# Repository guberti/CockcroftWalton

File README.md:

# 40 kV 10 mA Cockcroft-Walton Multiplier
To power a Farnsworth-Hirsch fusor me and some other [@EastsidePreparatorySchool](https://github.com/EastsidePreparatorySchool) students are building, we calculated we would need 10 mA of DC current, since the amount of radiation produced is proportional to the **square** of the voltage.

In this repo you can see the files needed to edit and order these circuit boards yourself. They are in EAGLE CAD format, and a ZIP file accepted by circuit board makers is also provided. 

The Cockcroft-Walton multiplier here is a two-stage full-wave multiplier. It is intended to be powered by a neon sign transformer that supplies 24 kV peak-to-peak AC at 30 mA in alternating phases. These are pretty cheap, and can be had on Ebay for ~$150. Note that you will need to remove the safety features of the NST before it can power these multipliers.

The circuit board, as printed, transforms this into +35 kV DC at 10 mA, though I intentionally installed the diodes backwards in my multiplier so it produces -35 kV instead (this is needed for deuterium fusion, since these ions are positively charged).

<p align="center"><i>Two stages of the soldered board. Blue jumper wires are present to stop the capacitors from building up charge.</i></p>

<p align="center"><i>The circuit board in EAGLE CAD</i></p>

<p align="center"><i>Voltage monitoring system for the CW circuit board. Note the level-shifted voltage dividers.</i></p>

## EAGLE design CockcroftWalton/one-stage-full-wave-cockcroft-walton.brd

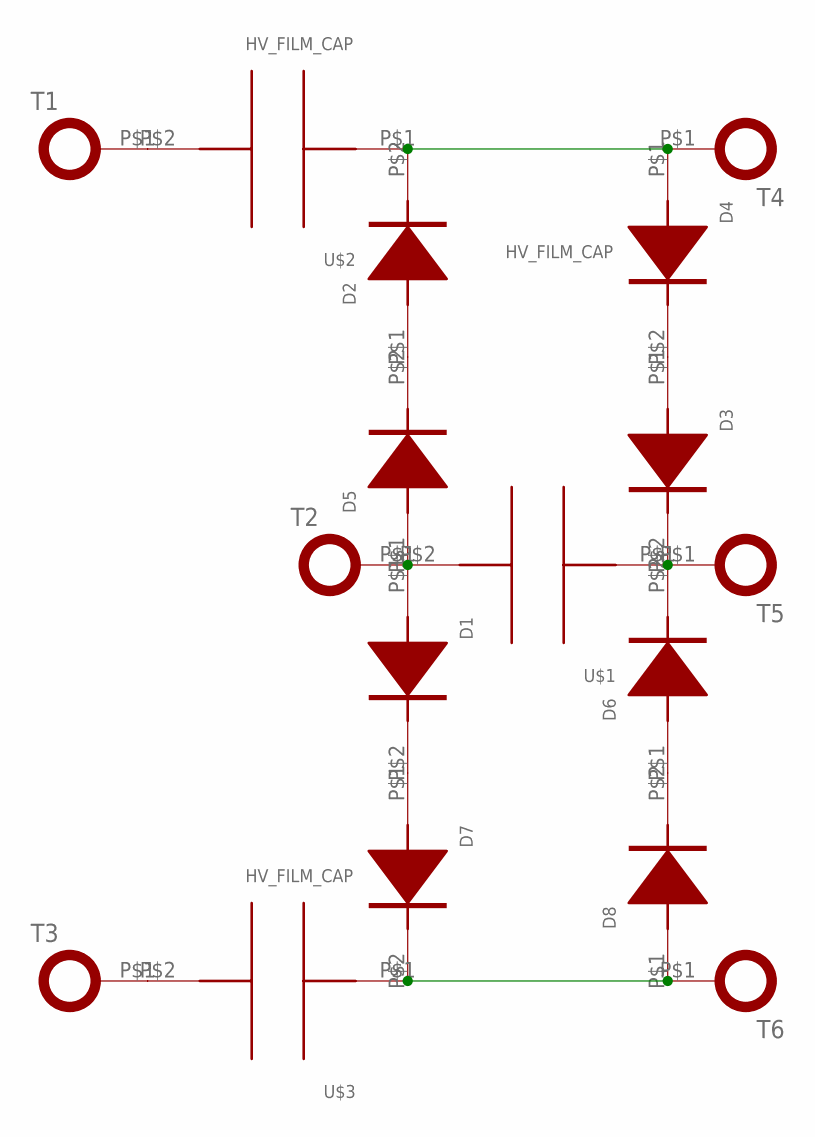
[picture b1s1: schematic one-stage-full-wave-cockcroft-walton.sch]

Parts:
D1, D2, D3, D4, D5, D6, D7, D8: DIODE_14MM; DIODE_14
T1, T2, T3, T4, T5, T6: TERMINAL_M6; LUG_SQUARE_M6
U$1, U$2, U$3: HV_FILM_CAP

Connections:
unnamed: D1.P$1 (ANODE), D5.P$1 (ANODE), T2.P$1, U$1.P$2
unnamed: D2.P$1 (ANODE), D5.P$2 (CATHODE)
unnamed: D2.P$2 (CATHODE), D4.P$1 (ANODE), T4.P$1, U$2.P$1
unnamed: D3.P$1 (ANODE), D4.P$2 (CATHODE)
unnamed: T3.P$1, U$3.P$2
unnamed: T1.P$1, U$2.P$2
unnamed: D7.P$2 (CATHODE), D8.P$1 (ANODE), T6.P$1, U$3.P$1
unnamed: D3.P$2 (CATHODE), D6.P$2 (CATHODE), T5.P$1, U$1.P$1
unnamed: D1.P$2 (CATHODE), D7.P$1 (ANODE)
unnamed: D6.P$1 (ANODE), D8.P$2 (CATHODE)

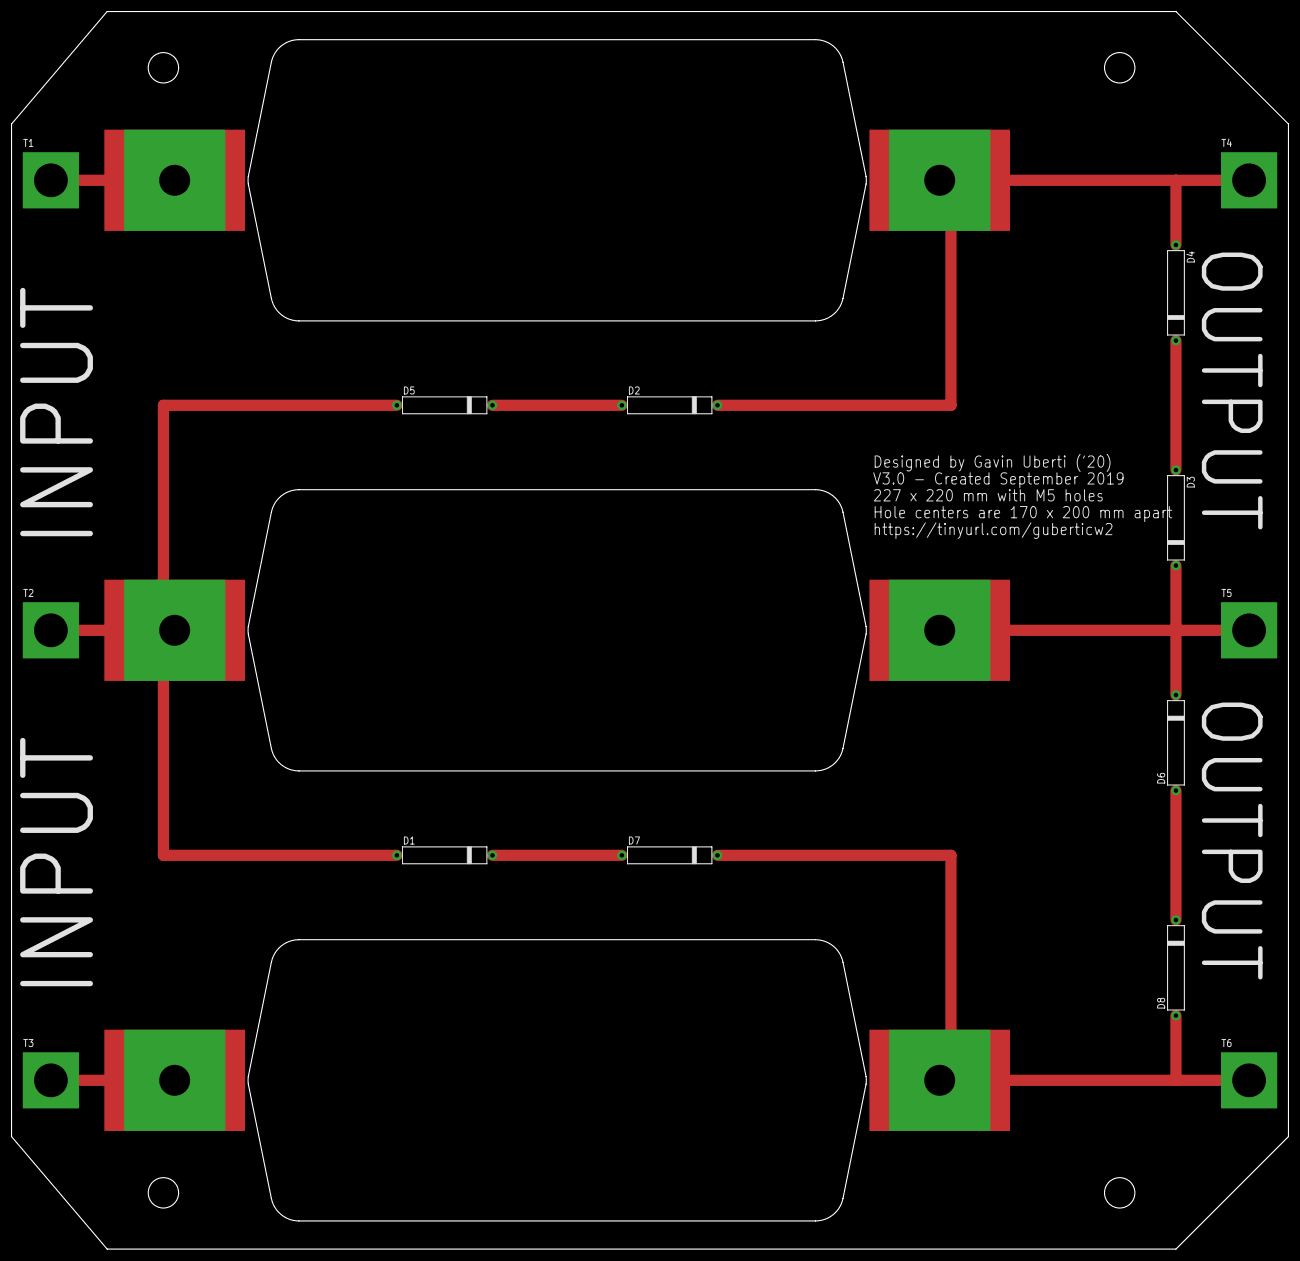
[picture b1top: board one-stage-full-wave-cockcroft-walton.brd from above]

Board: 2 copper layers, 227.0 x 220.0 mm, 17 parts (0 on the bottom side), 10 nets.

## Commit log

2019-10-03 Update README.md with information about project
2019-10-03 File dump
